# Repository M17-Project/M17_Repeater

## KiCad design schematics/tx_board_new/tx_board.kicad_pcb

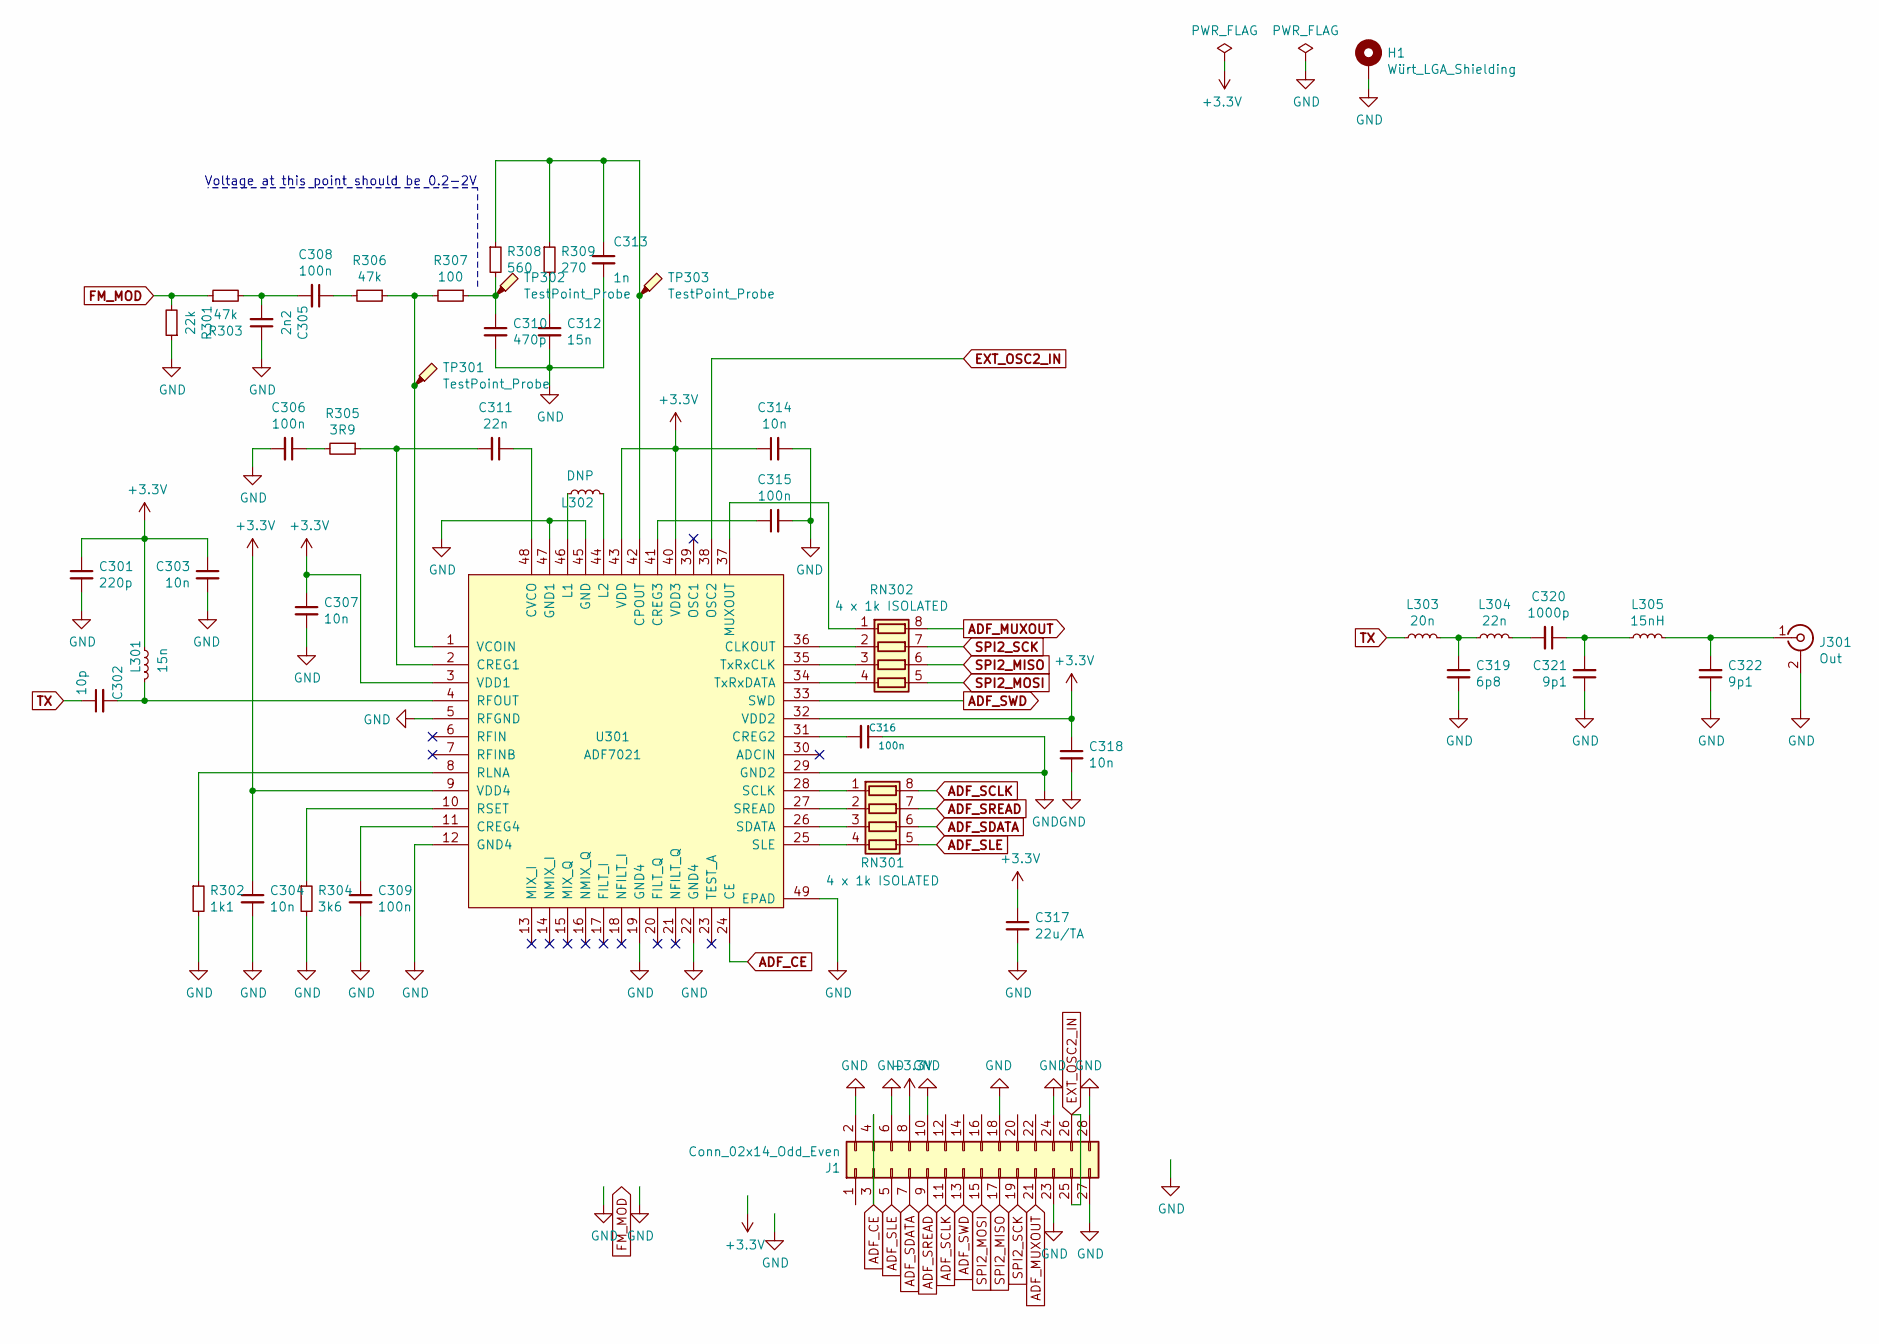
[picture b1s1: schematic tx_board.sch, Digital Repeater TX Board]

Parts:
C301: 220p; C_0603_1608Metric_Pad1.05x0.95mm_HandSolder; Voltage 50; Tolerance 5
C302: 10p; C_0603_1608Metric_Pad1.05x0.95mm_HandSolder; Voltage 50; Tolerance 5
C303, C304, C307, C314, C318: 10n; C_0603_1608Metric_Pad1.05x0.95mm_HandSolder; Tolerance 10; Voltage 50
C305: 2n2; C_0603_1608Metric_Pad1.05x0.95mm_HandSolder; Voltage 50; Tolerance 5
C306, C308, C309, C315, C316: 100n; C_0603_1608Metric_Pad1.05x0.95mm_HandSolder; Voltage 50; Tolerance 10
C310: 470p; C_0603_1608Metric_Pad1.05x0.95mm_HandSolder; Voltage 50; Tolerance 5
C311: 22n; C_0603_1608Metric_Pad1.05x0.95mm_HandSolder; Voltage 50; Tolerance 10
C312: 15n; C_0603_1608Metric_Pad1.05x0.95mm_HandSolder; Voltage 50; Tolerance 10
C313: 1n; C_0603_1608Metric_Pad1.05x0.95mm_HandSolder; Voltage 50; Tolerance 10
C317: 22u/TA; CP_EIA-3216-18_Kemet-A_Pad1.58x1.35mm_HandSolder; Tolerance 10; Voltage 10; Partno TAJA226K006RNJV
C319: 6p8; C_0603_1608Metric_Pad1.05x0.95mm_HandSolder; Voltage 50; Tolerance 5
C320: 1000p; C_0603_1608Metric_Pad1.05x0.95mm_HandSolder; Voltage 50; Tolerance 5
C321, C322: 9p1; C_0603_1608Metric_Pad1.05x0.95mm_HandSolder; Voltage 50; Tolerance 5
H1: Würt_LGA_Shielding; WE_36103205_SMD
J1: Conn_02x14_Odd_Even; edge_2x14pin
J301: Out; SMA_Samtec_SMA-J-P-X-ST-EM1_EdgeMount
L301: 15n; L_0603_1608Metric_Pad1.05x0.95mm_HandSolder
L302: DNP; L_0603_1608Metric_Pad1.05x0.95mm_HandSolder
L303: 20n; L_0603_1608Metric_Pad1.05x0.95mm_HandSolder
L304: 22n; L_0603_1608Metric_Pad1.05x0.95mm_HandSolder
L305: 15nH; L_0603_1608Metric_Pad1.05x0.95mm_HandSolder
R301: 22k; R_0603_1608Metric_Pad1.05x0.95mm_HandSolder; Tolerance 5
R302: 1k1; R_0603_1608Metric_Pad1.05x0.95mm_HandSolder; Tolerance 5
R303, R306: 47k; R_0603_1608Metric_Pad1.05x0.95mm_HandSolder; Tolerance 5
R304: 3k6; R_0603_1608Metric_Pad1.05x0.95mm_HandSolder; Tolerance 5
R305: 3R9; R_0603_1608Metric_Pad1.05x0.95mm_HandSolder; Tolerance 5
R307: 100; R_0603_1608Metric_Pad1.05x0.95mm_HandSolder; Tolerance 5
R308: 560; R_0603_1608Metric_Pad1.05x0.95mm_HandSolder; Tolerance 5
R309: 270; R_0603_1608Metric_Pad1.05x0.95mm_HandSolder; Tolerance 5
RN301, RN302: 4 x 1k ISOLATED; R_Array_Concave_4x0603; Tolerance 5
TP301, TP302, TP303: TestPoint_Probe; TestPoint_Pad_D1.0mm
U301: ADF7021; LFCSP-48-1EP_7x7mm_P0.5mm_EP4.1x4.1mm_ThermalVias

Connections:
+3V3: C301.1, C303.1, C304.1, C307.1, C314.1, C317.1, C318.1, J1.8, L301.1, U301.3 (VDD1), U301.9 (VDD4), U301.32 (VDD2), U301.40 (VDD3), U301.43 (VDD)
ADF_CE: J1.3, J1.4, U301.24 (CE)
ADF_MUXOUT: J1.21, RN302.8 (R1.2)
ADF_SCLK: J1.11, RN301.8 (R1.2)
ADF_SDATA: J1.7, RN301.6 (R3.2)
ADF_SLE: J1.5, RN301.5 (R4.2)
ADF_SREAD: J1.9, RN301.7 (R2.2)
ADF_SWD: J1.13, U301.33 (SWD)
EXT_OSC2_IN: J1.25, J1.26, U301.38 (OSC2)
FM_MOD: R301.2, R303.1
GND: C301.2, C303.2, C304.2, C305.1, C306.2, C307.2, C309.2, C310.2, C312.2, C313.2, C314.2, C315.2, C316.1, C317.2, C318.2, C319.2, C321.1, C322.1, H1.1, J1.2, J1.6, J1.10, J1.18, J1.23, J1.24, J1.27, J1.28, J301.2 (Ext), R301.1, R302.2, R304.2, U301.5 (RFGND), U301.12 (GND4), U301.19 (GND4), U301.22 (GND4), U301.29 (GND2), U301.45 (GND), U301.47 (GND1), U301.49 (EPAD)
unnamed: C302.2, L301.2, U301.4 (RFOUT)
unnamed: C305.2, C308.2, R303.2
unnamed: C306.1, R305.2
unnamed: C308.1, R306.2
unnamed: C309.1, U301.11 (CREG4)
unnamed: C310.1, R307.1, R308.2, TP302.1
unnamed: C311.1, U301.48 (CVCO)
unnamed: C311.2, R305.1, U301.2 (CREG1)
unnamed: C312.1, R309.2
unnamed: C313.1, R308.1, R309.1, TP303.1, U301.42 (CPOUT)
unnamed: C315.1, U301.41 (CREG3)
unnamed: C316.2, U301.31 (CREG2)
unnamed: C319.1, L303.2, L304.1
unnamed: C320.1, C321.2, L305.1
unnamed: C320.2, L304.2
unnamed: C322.2, J301.1 (In), L305.2
unnamed: L302.1, U301.46 (L1)
unnamed: L302.2, U301.44 (L2)
unnamed: R302.1, U301.8 (RLNA)
unnamed: R304.1, U301.10 (RSET)
unnamed: R306.1, R307.2, TP301.1, U301.1 (VCOIN)
unnamed: RN301.1 (R1.1), U301.28 (SCLK)
unnamed: RN301.2 (R2.1), U301.27 (SREAD)
unnamed: RN301.3 (R3.1), U301.26 (SDATA)
unnamed: RN301.4 (R4.1), U301.25 (SLE)
unnamed: RN302.1 (R1.1), U301.37 (MUXOUT)
unnamed: RN302.2 (R2.1), U301.36 (CLKOUT)
unnamed: RN302.3 (R3.1), U301.35 (TxRxCLK)
unnamed: RN302.4 (R4.1), U301.34 (TxRxDATA)
SPI2_MISO: J1.17, RN302.6 (R3.2)
SPI2_MOSI: J1.15, RN302.5 (R4.2)
SPI2_SCK: J1.19, RN302.7 (R2.2)
TX: C302.1, L303.1

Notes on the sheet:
Voltage at this point should be 0.2-2V

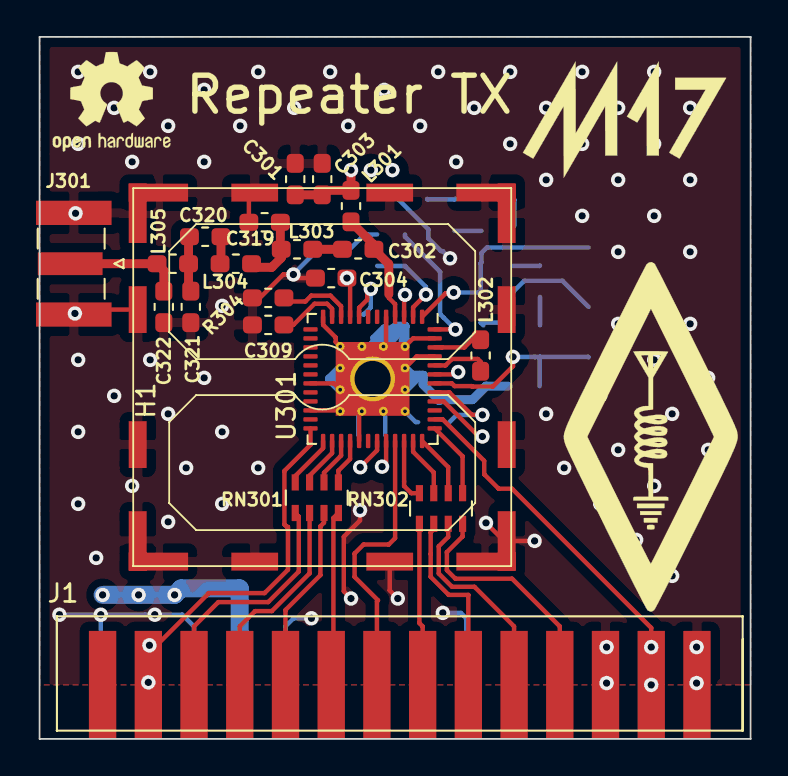
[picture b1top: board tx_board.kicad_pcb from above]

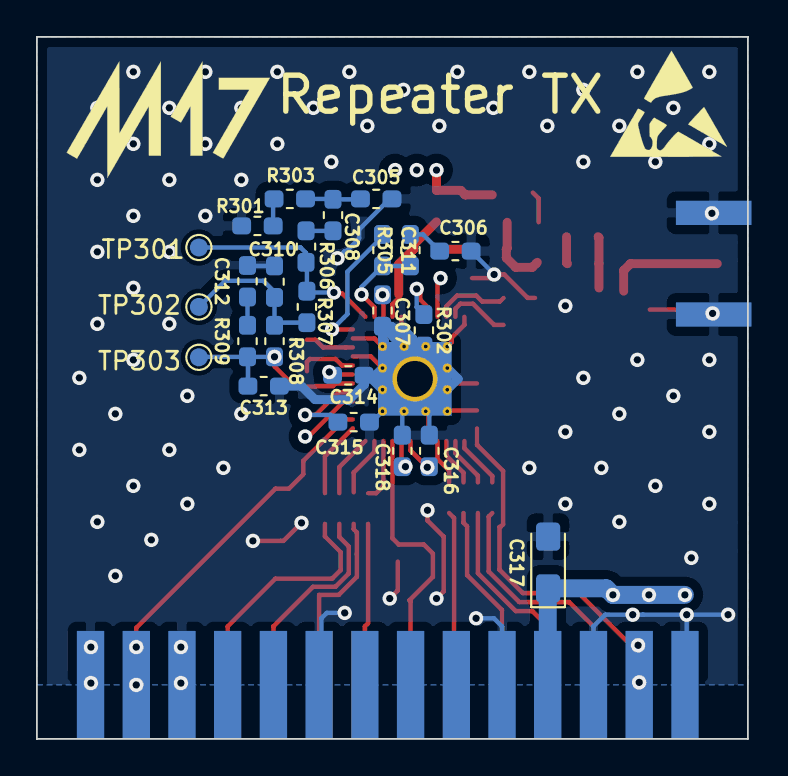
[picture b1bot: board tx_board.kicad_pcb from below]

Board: 4 copper layers, 39.5 x 39.0 mm, 45 parts (24 on the bottom side), 44 nets.

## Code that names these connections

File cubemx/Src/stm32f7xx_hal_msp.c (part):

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    __HAL_RCC_SPI2_CLK_ENABLE();
  
    /**SPI2 GPIO Configuration    
    PB13     ------> SPI2_SCK
    PB14     ------> SPI2_MISO
    PB15     ------> SPI2_MOSI 
    */
    GPIO_InitStruct.Pin = TX_SCK_Pin|TX_MISO_Pin|TX_MOSI_Pin;
    GPIO_InitStruct.Mode = GPIO_MODE_AF_PP;
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    __HAL_RCC_SPI2_CLK_DISABLE();
  
    /**SPI2 GPIO Configuration    
    PB13     ------> SPI2_SCK
    PB14     ------> SPI2_MISO
    PB15     ------> SPI2_MOSI 
    */
    HAL_GPIO_DeInit(GPIOB, TX_SCK_Pin|TX_MISO_Pin|TX_MOSI_Pin);

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

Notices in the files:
cubemx/Src/stm32f7xx_hal_msp.c:
COPYRIGHT(c) 2019 STMicroelectronics
(C) COPYRIGHT STMicroelectronics *****END OF FILE
